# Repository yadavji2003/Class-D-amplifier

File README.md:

# Class-D-amplifier
In this project, i have made class D amplifier without using specific IC 
# REQUIRED ELEMENTS
LM324
NE555D
IRLZ34N
SPEAKER
 Now Explain Each
 LM324: versatile — use it for the audio preamp, triangle oscillator (op-amp integrator + comparator), PWM comparator, and feedback amplifier. LM324 runs single-supply and can handle inputs near ground (handy).

NE555D: can be used as a stable high-frequency oscillator (gives square / ramp-ish at the timing capacitor) or as a timing/delay element to create dead-time or inverted PWM. If you prefer a purer triangle, use LM324 op-amp integrator + comparator instead.

IRLZ34N: N-channel MOSFETs for the switching output stage. They are logic-level, low Rds(on) when driven properly — used as switches in an H-bridge or half-bridge.
SPEAKER: It is output of the project .it connect to drain and source terminal of the MOSFET.
#

Here are the full forms of the main components used in your Class-D amplifier circuit:

PWM → Pulse Width Modulation

NE555D → “NE” stands for Manufacturer Series (by Signetics/Philips), and “555” is the Timer IC number. The suffix D usually means SOIC package (Surface-mount Dual). So full form:
→ NE555 Timer IC (Dual-In-line / Surface-mount package)

LM324 → Linear Monolithic 324 (a Quad Operational Amplifier)

“LM” means Linear Monolithic (Texas Instruments / National Semiconductor series).

“324” is the specific model — contains 4 op-amps in one chip.

IRLZ34N → International Rectifier Logic-Level Z-series 34 A N-channel MOSFET

IR → International Rectifier (original manufacturer)

L → Logic-level gate drive

Z → Advanced hexFET family

34 → Approximate drain current rating (34 A)

N → N-channel MOSFET

So, summarizing simply:

Symbol	Full Form / Meaning
PWM	Pulse Width Modulation
NE555D	Timer IC (NE series, 555 model, D = surface-mount)
LM324	Linear Monolithic Quad Operational Amplifier
IRLZ34N	International Rectifier Logic-Level N-Channel MOSFET (34 A)

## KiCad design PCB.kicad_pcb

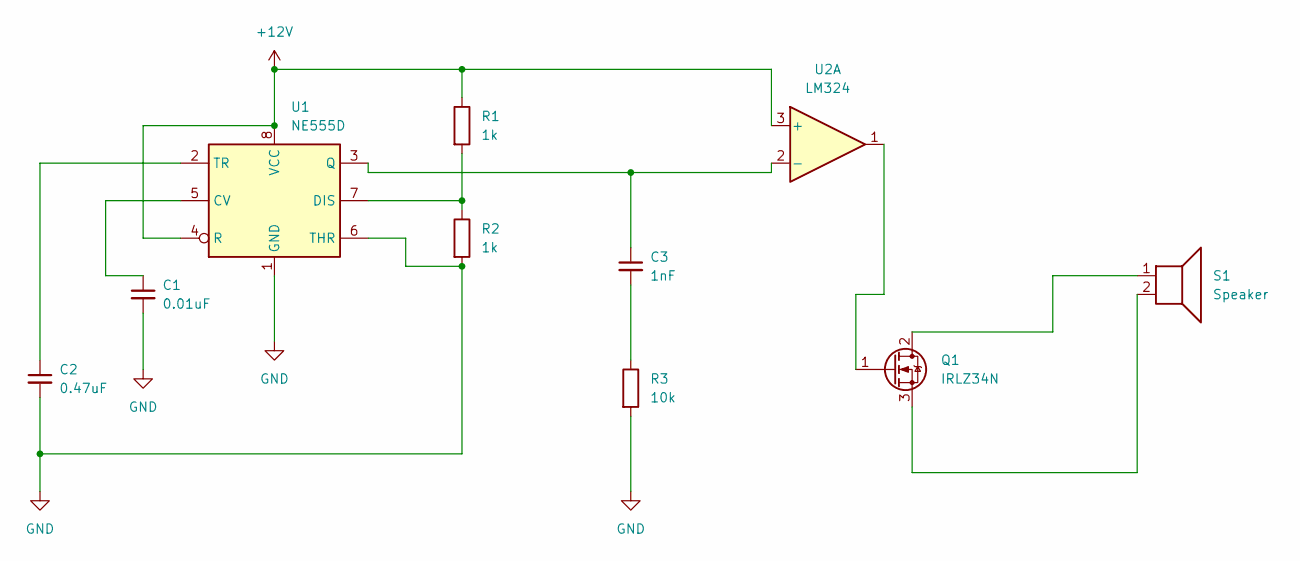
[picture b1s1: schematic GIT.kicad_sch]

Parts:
C1: 0.01uF; C_0805_2012Metric
C2: 0.47uF; C_0805_2012Metric
C3: 1nF; C_0805_2012Metric
Q1: IRLZ34N; TO-220-3_Vertical
R1, R2: 1k; R_0508_1220Metric
R3: 10k; C_0805_2012Metric
S1: Speaker; Speaker_CUI_CMR-1206S-67
U1: NE555D; SOIC-8_3.9x4.9mm_P1.27mm
U2: LM324; SSOP-14_5.3x6.2mm_P0.65mm

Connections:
+12V: R1.1, U1.4 (R), U1.8 (VCC), U2.3 (+)
GND: C1.2, C2.2, R2.2, R3.2, U1.1 (GND), U1.6 (THR)
unnamed: C3.2, R3.1
unnamed: Q1.2 (D), S1.1
unnamed: Q1.1 (G), U2.1
unnamed: Q1.3 (S), S1.2
unnamed: C1.1, U1.5 (CV)
unnamed: R1.2, R2.1, U1.7 (DIS)
unnamed: C3.1, U1.3 (Q), U2.2 (-)
unnamed: C2.1, U1.2 (TR)

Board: 2 copper layers, 10 parts (0 on the bottom side), 10 nets, no tracks yet.
